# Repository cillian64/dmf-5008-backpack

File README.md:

# dmf-5008-backpack
Controller backpack for Optrex DMF-5008N-S display

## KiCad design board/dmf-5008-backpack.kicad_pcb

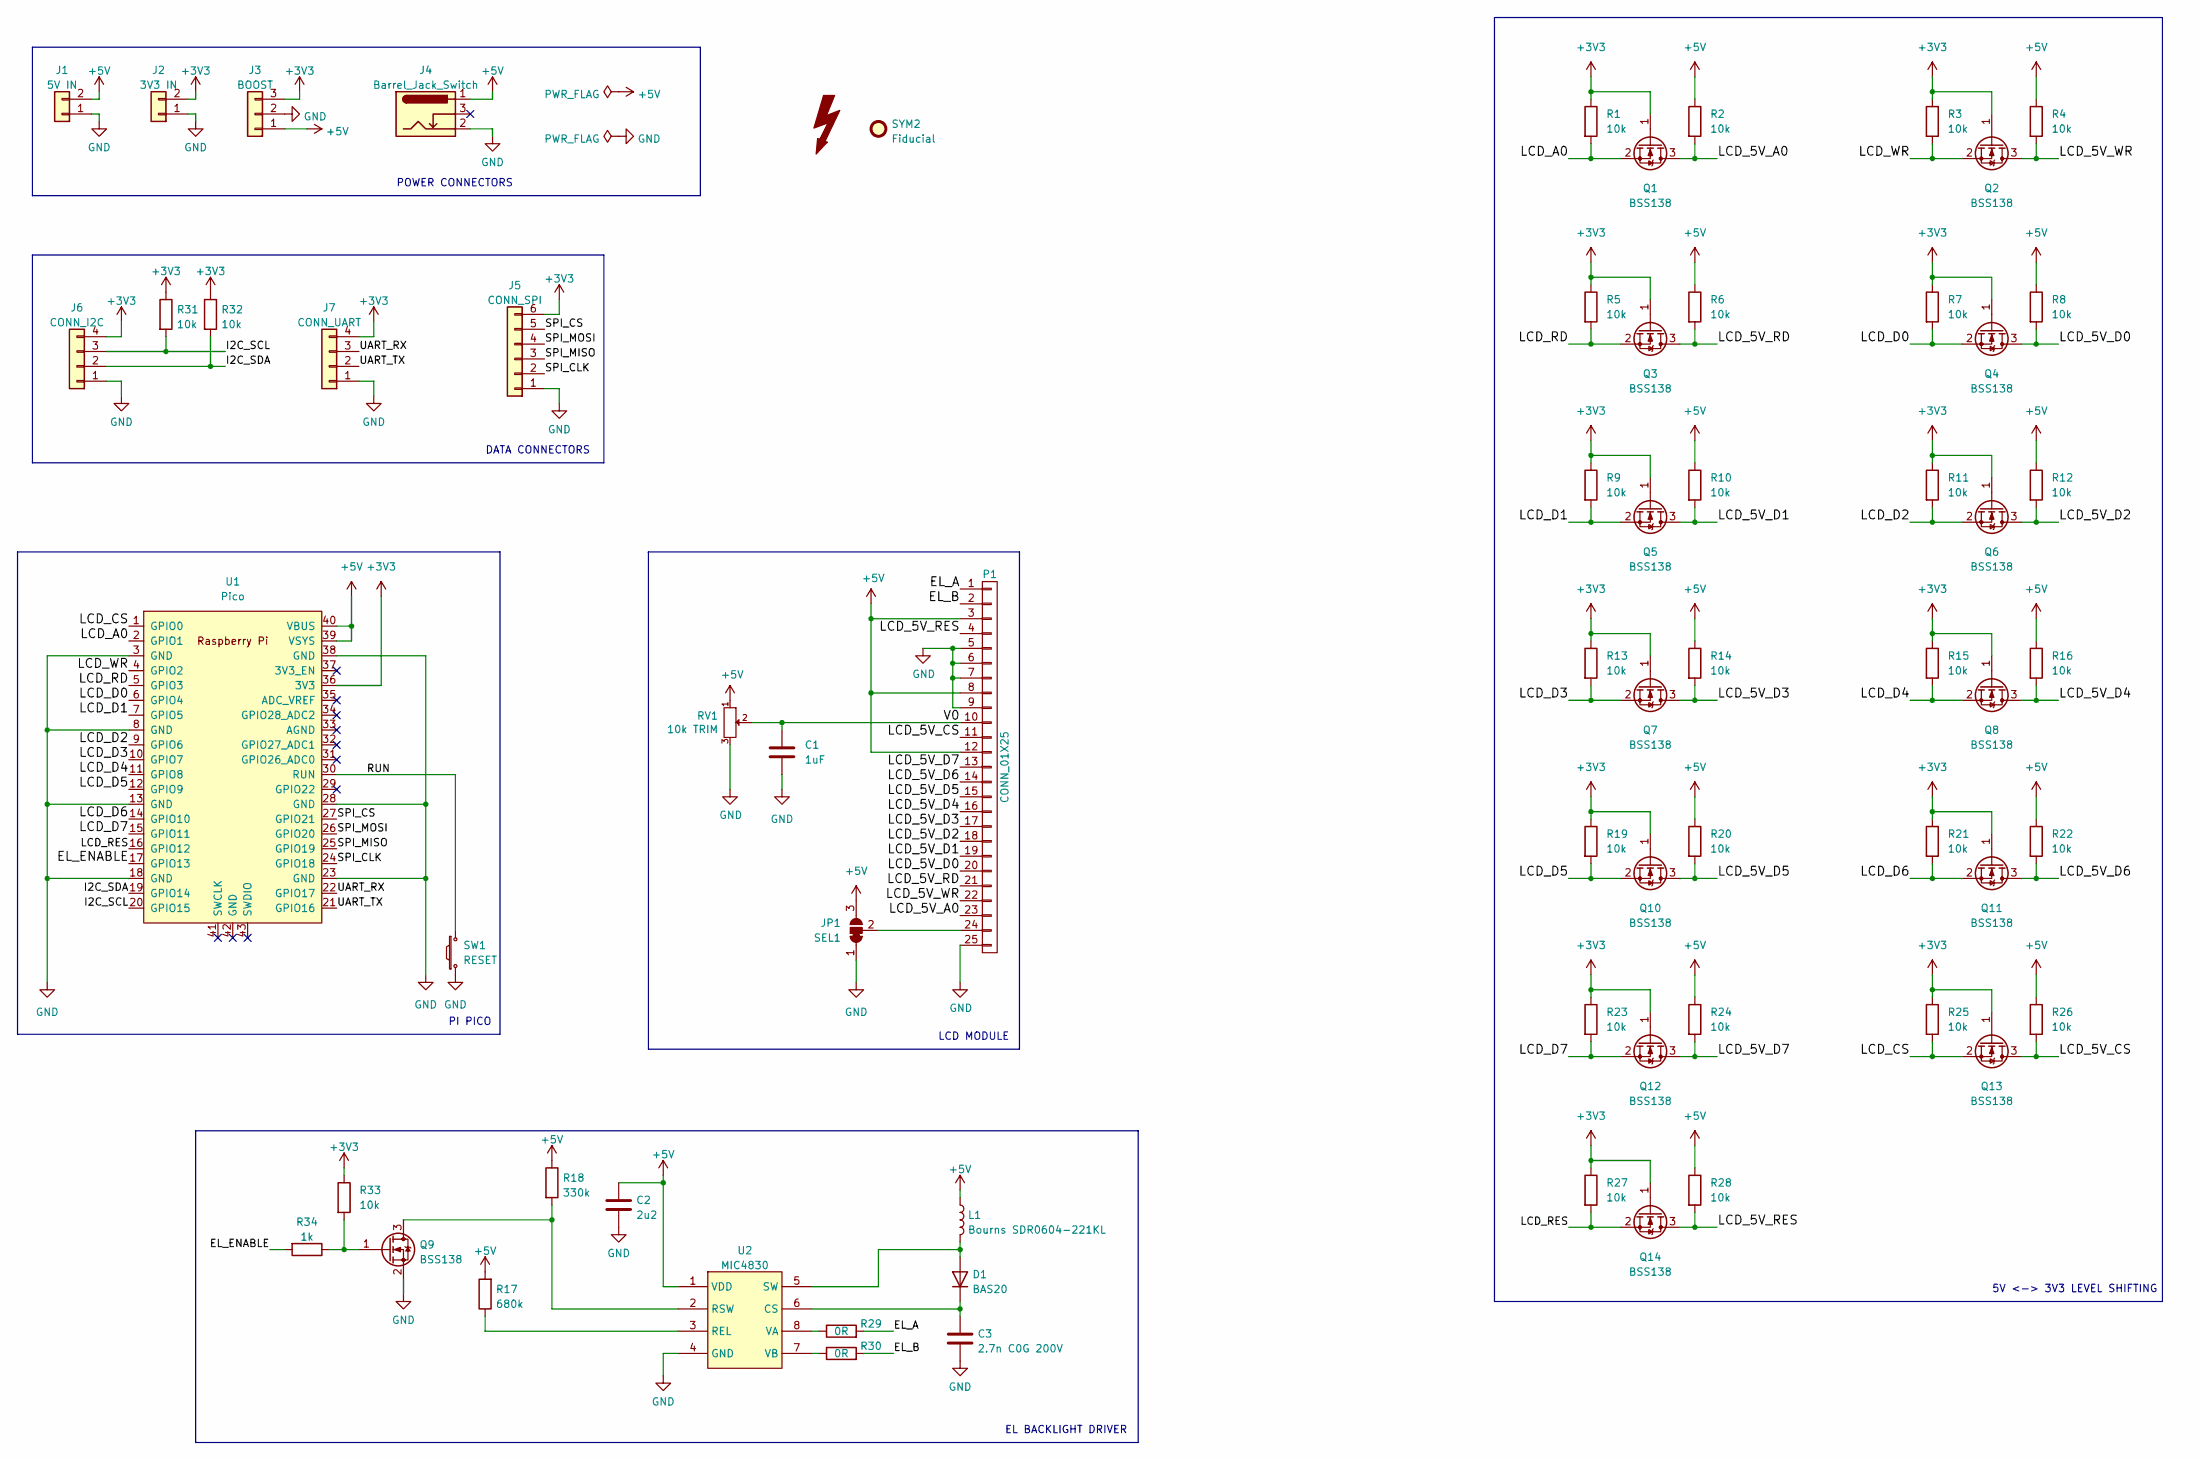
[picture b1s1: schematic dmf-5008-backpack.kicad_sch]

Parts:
C1: 1uF; C_0805_2012Metric
C2: 2u2; C_0805_2012Metric
C3: 2.7n C0G 200V; C_0805_2012Metric_Pad1.18x1.45mm_HandSolder
D1: BAS20; SOT-23
J1: 5V IN; PinHeader_1x02_P2.54mm_Vertical
J2: 3V3 IN; PinHeader_1x02_P2.54mm_Vertical
J3: BOOST; PinHeader_1x03_P2.54mm_Vertical
J4: Barrel_Jack_Switch; BarrelJack_Horizontal
J5: CONN_SPI; PinHeader_1x06_P2.54mm_Vertical
J6: CONN_I2C; PinHeader_1x04_P2.54mm_Vertical
J7: CONN_UART; PinHeader_1x04_P2.54mm_Vertical
JP1: SEL1; SolderJumper-3_P1.3mm_Bridged12_RoundedPad1.0x1.5mm_NumberL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
L1: Bourns SDR0604-221KL; L_Bourns_SRN6045TA
P1: CONN_01X25; lcd_full
Q1, Q2, Q3, Q4, Q5, Q6, Q7, Q8, Q9, Q10, Q11, Q12, Q13, Q14: BSS138; SOT-23
R1, R2, R3, R4, R5, R6, R7, R8, R9, R10, R11, R12, R13, R14, R15, R16, R19, R20, R21, R22, R23, R24, R25, R26, R27, R28, R31, R32, R33: 10k; R_0603_1608Metric
R17: 680k; R_0603_1608Metric
R18: 330k; R_0603_1608Metric
R29, R30: 0R; R_1206_3216Metric_Pad1.30x1.75mm_HandSolder
R34: 1k; R_0603_1608Metric
RV1: 10k TRIM; Potentiometer_ACP_CA9-V10_Vertical
SW1: RESET; SW_PUSH_6mm
SYM1: SYM_Flash_Large; Symbol_Highvoltage_Type2_CopperTop_Small
SYM2: Fiducial; Symbol_Barrel_Polarity
U1: Pico; RPi_Pico_SMD_TH
U2: MIC4830; MSOP-8_3x3mm_P0.65mm

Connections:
+3V3: J2.2, J3.3, J5.6, J6.4, J7.4, Q1.1 (G), Q2.1 (G), Q3.1 (G), Q4.1 (G), Q5.1 (G), Q6.1 (G), Q7.1 (G), Q8.1 (G), Q10.1 (G), Q11.1 (G), Q12.1 (G), Q13.1 (G), Q14.1 (G), R1.1, R3.1, R5.1, R7.1, R9.1, R11.1, R13.1, R15.1, R19.1, R21.1, R23.1, R25.1, R27.1, R31.1, R32.1, R33.1, U1.36 (3V3)
+5V: C2.1, J1.2, J3.1, J4.1, JP1.3 (B), L1.1, P1.3, P1.8, P1.12, R2.1, R4.1, R6.1, R8.1, R10.1, R12.1, R14.1, R16.1, R17.2, R18.1, R20.1, R22.1, R24.1, R26.1, R28.1, RV1.1, U1.39 (VSYS), U1.40 (VBUS), U2.1 (VDD)
/EL_A: P1.1, R29.2
/EL_B: P1.2, R30.2
/EL_ENABLE: R34.2, U1.17 (GPIO13)
/I2C_SCL: J6.3, R31.2, U1.20 (GPIO15)
/I2C_SDA: J6.2, R32.2, U1.19 (GPIO14)
/LCD_5V_A0: P1.23, Q1.3 (D), R2.2
/LCD_5V_CS: P1.11, Q13.3 (D), R26.2
/LCD_5V_D0: P1.20, Q4.3 (D), R8.2
/LCD_5V_D1: P1.19, Q5.3 (D), R10.2
/LCD_5V_D2: P1.18, Q6.3 (D), R12.2
/LCD_5V_D3: P1.17, Q7.3 (D), R14.2
/LCD_5V_D4: P1.16, Q8.3 (D), R16.2
/LCD_5V_D5: P1.15, Q10.3 (D), R20.2
/LCD_5V_D6: P1.14, Q11.3 (D), R22.2
/LCD_5V_D7: P1.13, Q12.3 (D), R24.2
/LCD_5V_RD: P1.21, Q3.3 (D), R6.2
/LCD_5V_RES: P1.4, Q14.3 (D), R28.2
/LCD_5V_WR: P1.22, Q2.3 (D), R4.2
/LCD_A0: Q1.2 (S), R1.2, U1.2 (GPIO1)
/LCD_CS: Q13.2 (S), R25.2, U1.1 (GPIO0)
/LCD_D0: Q4.2 (S), R7.2, U1.6 (GPIO4)
/LCD_D1: Q5.2 (S), R9.2, U1.7 (GPIO5)
/LCD_D2: Q6.2 (S), R11.2, U1.9 (GPIO6)
/LCD_D3: Q7.2 (S), R13.2, U1.10 (GPIO7)
/LCD_D4: Q8.2 (S), R15.2, U1.11 (GPIO8)
/LCD_D5: Q10.2 (S), R19.2, U1.12 (GPIO9)
/LCD_D6: Q11.2 (S), R21.2, U1.14 (GPIO10)
/LCD_D7: Q12.2 (S), R23.2, U1.15 (GPIO11)
/LCD_RD: Q3.2 (S), R5.2, U1.5 (GPIO3)
/LCD_RES: Q14.2 (S), R27.2, U1.16 (GPIO12)
/LCD_WR: Q2.2 (S), R3.2, U1.4 (GPIO2)
/RUN: SW1.2, U1.30 (RUN)
/SPI_CLK: J5.2, U1.24 (GPIO18)
/SPI_CS: J5.5, U1.27 (GPIO21)
/SPI_MISO: J5.3, U1.25 (GPIO19)
/SPI_MOSI: J5.4, U1.26 (GPIO20)
/UART_RX: J7.3, U1.22 (GPIO17)
/UART_TX: J7.2, U1.21 (GPIO16)
/V0: C1.1, P1.10, RV1.2
GND: C1.2, C2.2, C3.2, J1.1, J2.1, J3.2, J4.2, J5.1, J6.1, J7.1, JP1.1 (A), P1.5, P1.6, P1.7, P1.9, P1.25, Q9.2 (S), RV1.3, SW1.1, U1.3 (GND), U1.8 (GND), U1.13 (GND), U1.18 (GND), U1.23 (GND), U1.28 (GND), U1.38 (GND), U2.4 (GND)
unnamed: C3.1, D1.3 (K), U2.6 (CS)
unnamed: D1.1 (A), L1.2, U2.5 (SW)
unnamed: JP1.2 (C), P1.24
unnamed: Q9.1 (G), R33.2, R34.1
unnamed: Q9.3 (D), R18.2, U2.2 (RSW)
unnamed: R17.1, U2.3 (REL)
unnamed: R29.1, U2.8 (VA)
unnamed: R30.1, U2.7 (VB)

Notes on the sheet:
PI PICO
DATA CONNECTORS
POWER CONNECTORS
5V <-> 3V3 LEVEL SHIFTING
EL BACKLIGHT DRIVER
LCD MODULE

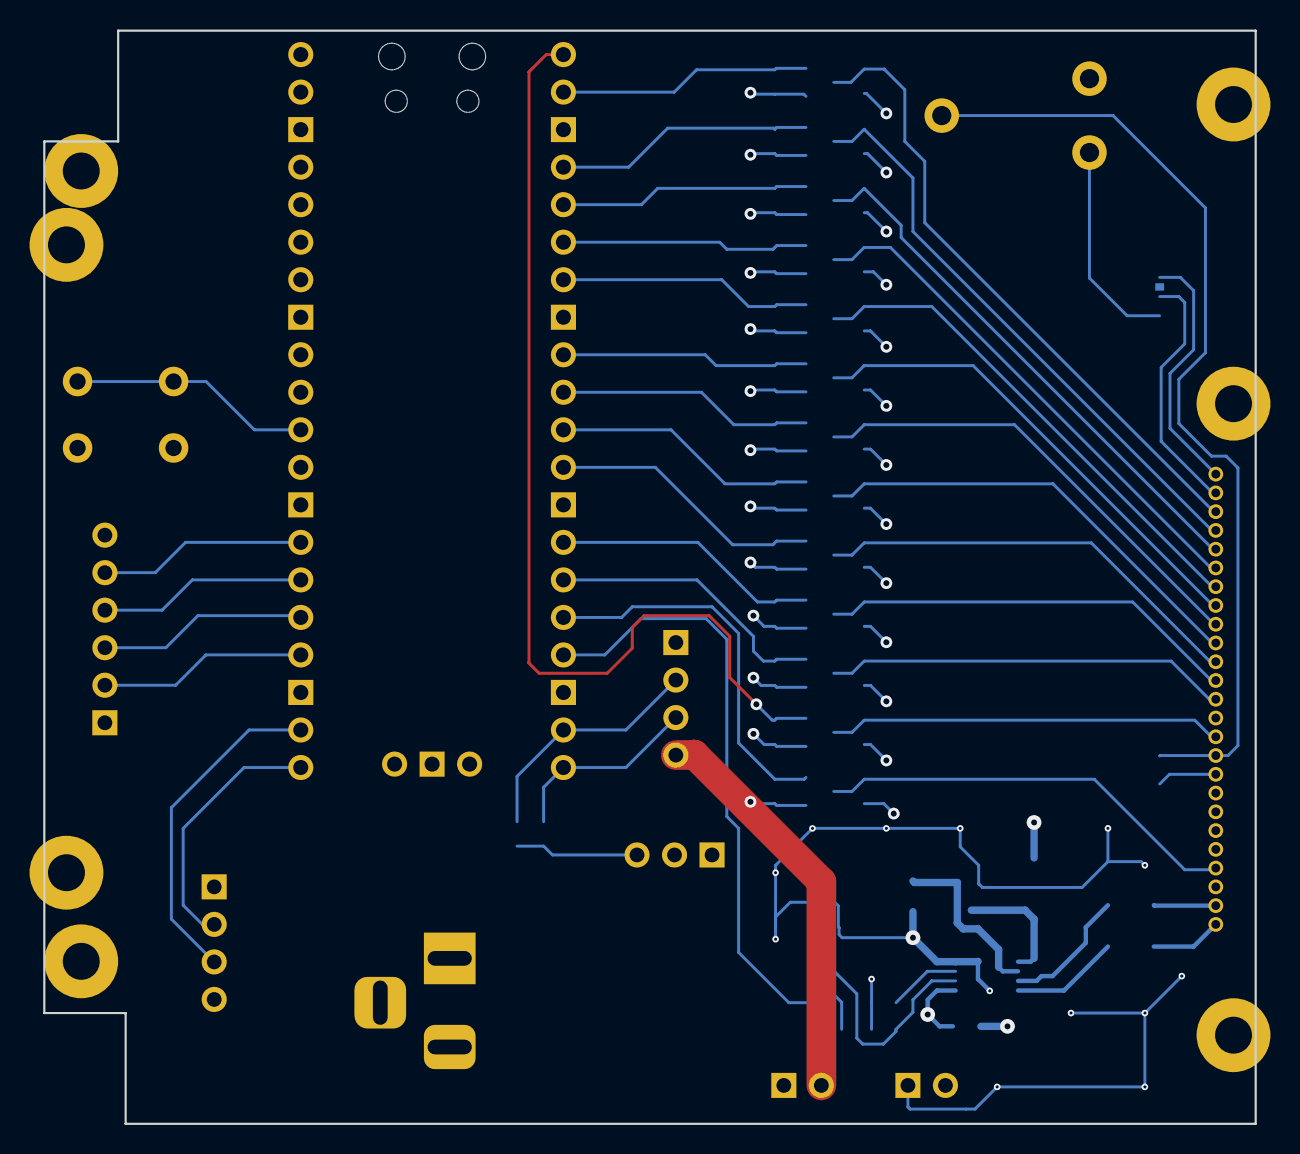
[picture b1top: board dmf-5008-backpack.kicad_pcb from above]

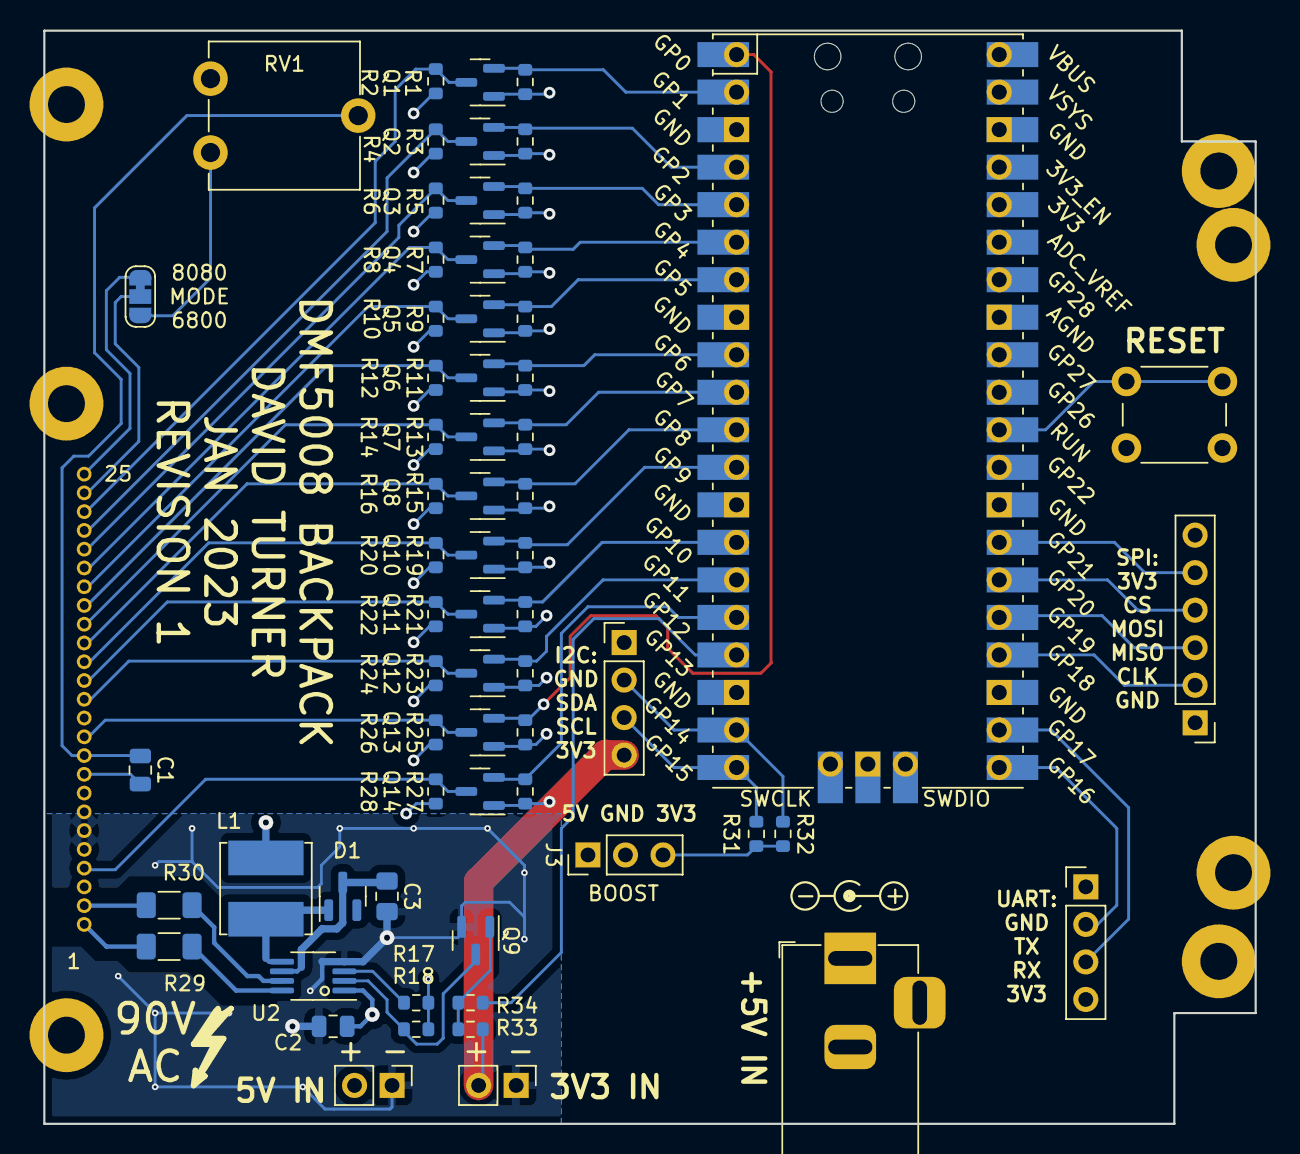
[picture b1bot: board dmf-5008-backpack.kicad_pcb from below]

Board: 4 copper layers, 82.0 x 74.0 mm, 68 parts (68 on the bottom side), 50 nets.

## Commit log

2017-02-02 Added empty board and agg-kicad
2017-02-02 various ramblings in README
2017-02-02 Initial checkin of gabotronics lcd library
2017-02-02 Modified copyright, began updates & cleanup
2017-02-02 added panel photos
2017-02-09 Started power supply stuff
2017-02-13 bump agg-kicad for max14521
2017-02-16 Change EL to simpler HV823 inverter
2017-02-16 filled in more circuit
    Did most STM32 support, LCD lines, step-up converter
2017-03-13 footprints
2022-12-03 Update file format to KiCAD 6
    Also rescue old symbols missing or changed in the new libraries.
2022-12-21 Rough draft of redesign around Pi Pico
2022-12-22 Update xformer and lcd footprints, add 3d models
2023-01-08 Rework schematic around MIC4830 EL driver
2023-01-22 Work on placement a bit
2023-01-22 Finish schematic, setup board capabilities
    * Finish schematic to checklist, happy with ERC
    * Add data connections and I2C pullups
    * Make EL_ENABLE an NPN pulldown, otherwise things will be confusing
    if R_SW is only pulled up to 3v3 by a GPIO.
    * Choose an inductor for the EL driver
    * Rough final placement of PCB
2023-01-22 PCB finished except for final checking
2023-01-31 Final checks and fixes
2023-01-31 Add production files (gerbers)
    Also add JLC database even though I won't be using the PCBA service.
2023-02-24 Add finalised BOM for PCB
2023-02-24 First rough prototype of python firmware
